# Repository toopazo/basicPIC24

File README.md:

basicPIC24
==========

Basic board to test and use the PIC24

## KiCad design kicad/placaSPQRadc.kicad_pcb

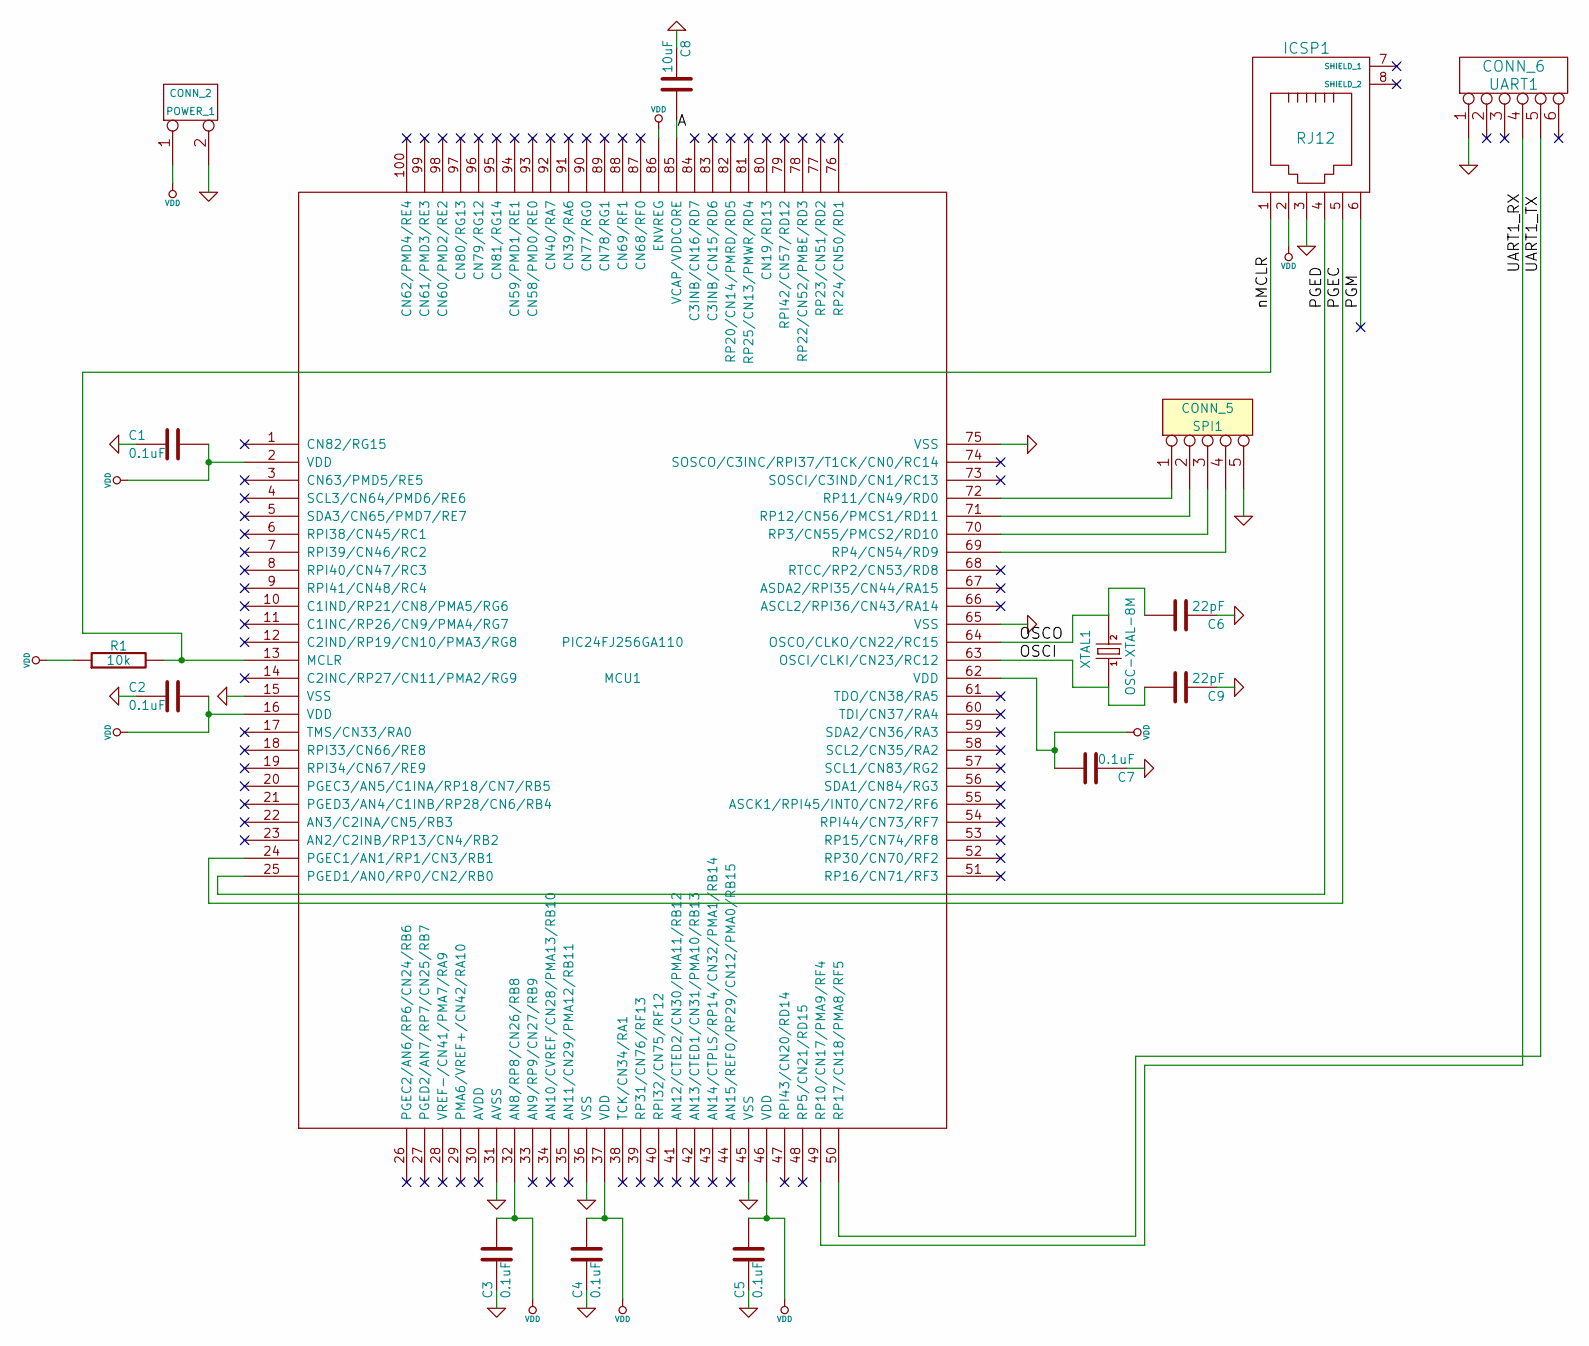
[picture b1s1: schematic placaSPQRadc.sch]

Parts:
C1, C2, C3, C4, C5, C7: 0.1uF
C6, C9: 22pF
C8: 10uF
ICSP1: RJ12
MCU1: PIC24FJ256GA110; MODULE
POWER_1: CONN_2
R1: 10k
SPI1: CONN_5
UART1: CONN_6
XTAL1: OSC-XTAL-8M; dp_devices-XTAL_5X8

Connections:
/A: C8.1, MCU1.85 (VCAP/VDDCORE)
/OSCI: C9.1, MCU1.63 (OSCI/CLKI/CN23/RC12), XTAL1.1
/OSCO: C6.1, MCU1.64 (OSCO/CLKO/CN22/RC15), XTAL1.2
/PGEC: ICSP1.5, MCU1.24 (PGEC1/AN1/RP1/CN3/RB1)
/PGED: ICSP1.4, MCU1.25 (PGED1/AN0/RP0/CN2/RB0)
/PGM: ICSP1.6
/UART1_RX: MCU1.49 (RP10/CN17/PMA9/RF4), UART1.4
/UART1_TX: MCU1.50 (RP17/CN18/PMA8/RF5), UART1.5
/nMCLR: ICSP1.1, MCU1.13 (MCLR), R1.2
GND: C1.2, C2.2, C3.2, C4.2, C5.2, C6.2, C7.2, C8.2, C9.2, ICSP1.3, MCU1.15 (VSS), MCU1.31 (AVSS), MCU1.36 (VSS), MCU1.45 (VSS), MCU1.65 (VSS), MCU1.75 (VSS), POWER_1.2 (PM), SPI1.5, UART1.1
unnamed: MCU1.69 (RP4/CN54/RD9), SPI1.4
unnamed: MCU1.70 (RP3/CN55/PMCS2/RD10), SPI1.3
unnamed: MCU1.71 (RP12/CN56/PMCS1/RD11), SPI1.2
unnamed: MCU1.72 (RP11/CN49/RD0), SPI1.1
VDD: C1.1, C2.1, C3.1, C4.1, C5.1, C7.1, ICSP1.2, MCU1.2 (VDD), MCU1.16 (VDD), MCU1.32 (AN8/RP8/CN26/RB8), MCU1.37 (VDD), MCU1.46 (VDD), MCU1.62 (VDD), MCU1.86 (ENVREG), POWER_1.1, R1.1

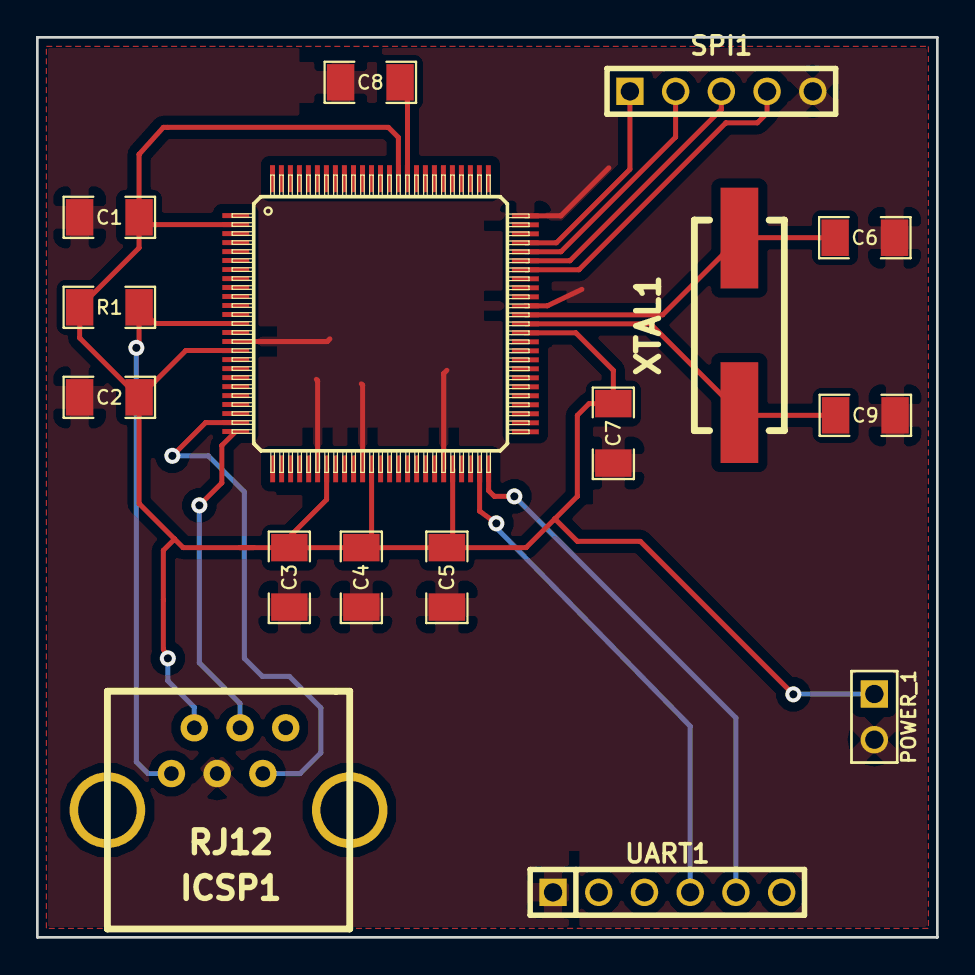
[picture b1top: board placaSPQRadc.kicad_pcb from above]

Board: 2 copper layers, 50.0 x 50.0 mm, 16 parts (0 on the bottom side), 14 nets.

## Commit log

2014-04-24 primera version de prueba para PCB, enviada a impresion con Miguel
2014-04-25 se modifica tamaño thermal relief
